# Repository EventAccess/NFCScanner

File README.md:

# NFCScanner
Maskinvare &amp; Firmware for in/ut-scanning

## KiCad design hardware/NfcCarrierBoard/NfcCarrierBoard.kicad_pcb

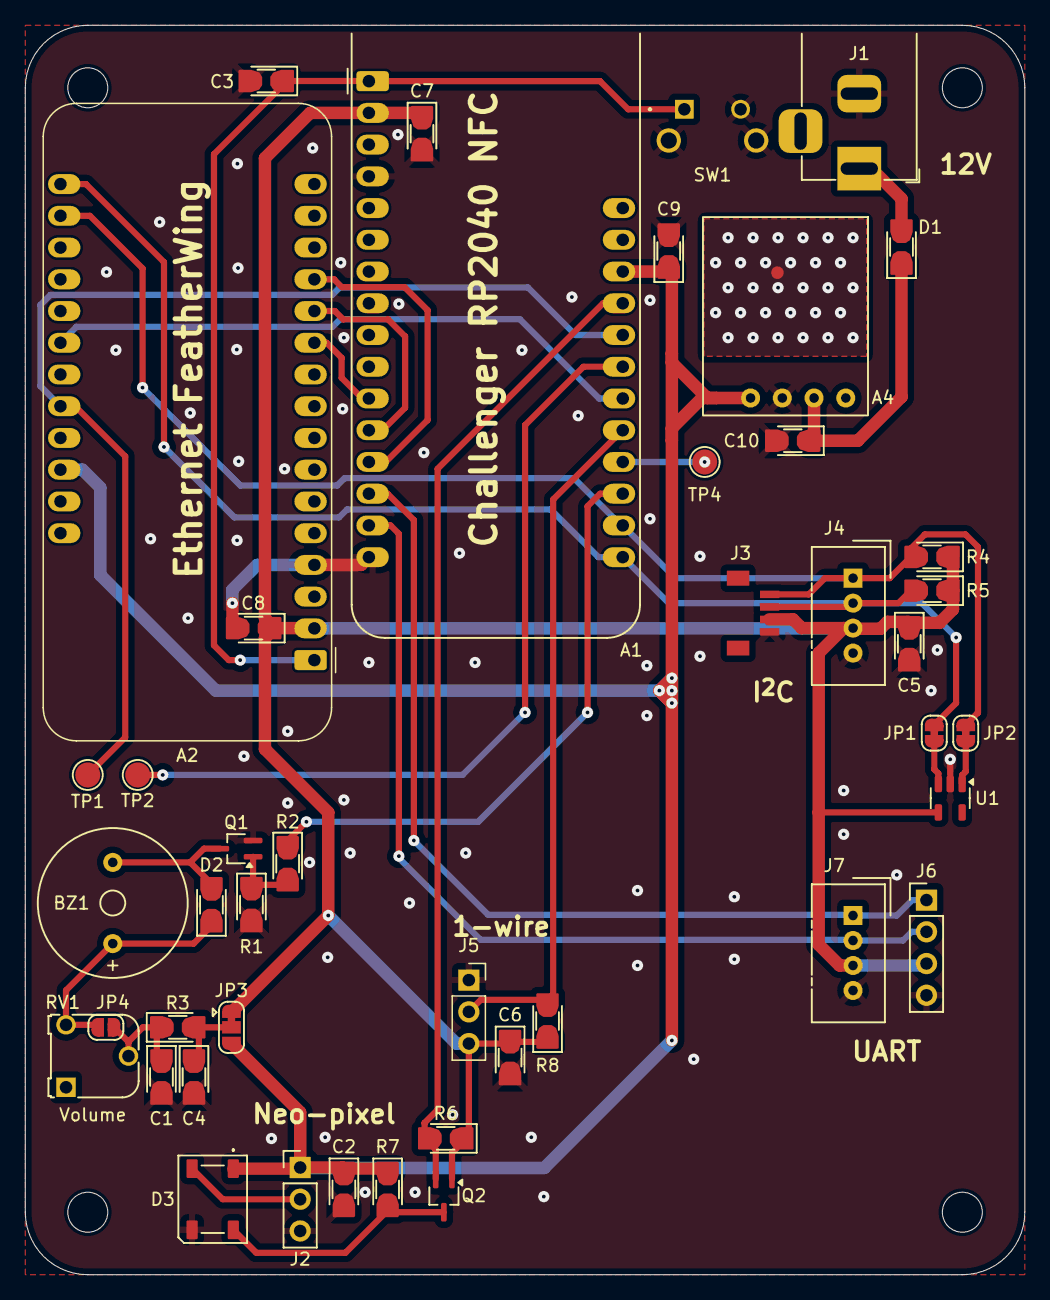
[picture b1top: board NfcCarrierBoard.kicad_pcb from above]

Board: 2 copper layers, 80.0 x 100.0 mm, 50 parts (1 on the bottom side), 29 nets.

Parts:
A1: iLabs Challenger RP2040 NFC; Adafruit_Feather
A2: Ethernet FeatherWing; Adafruit_Feather
A4: 5V 3A Buck Reg; SparkFun BabyBuck Regulator 5V
BZ1: Buzzer; Buzzer_PUIaudio_AT-1224-TWT_D12_H9_6.5mm
C1: 10µF; SMD_HANDSOLDER_UNIVERSAL_0603_0805_1206
C2, C3, C4, C5, C6, C7, C8, C9, C10: 0.1µF; SMD_HANDSOLDER_UNIVERSAL_0603_0805_1206
D1, D2: SL54A; SMD_HANDSOLDER_UNIVERSAL_0603_0805_1206
D3: WS2812B; LED_WS2812B_PLCC4_5.0x5.0mm_P3.2mm
H1, H2, H3, H4: MountingHole; MountingHole_3.2mm_M3
HS1: TestPoint; TestPoint_Pad_D1.0mm
J1: Barrel_Jack; BarrelJack_Horizontal
J2: Conn_01x03; PinHeader_1x03_P2.54mm_Vertical
J3: JST SH 4; JST-SH-4-top
J4: Grove; NS-Tech_Grove_1x04_P2mm_Vertical
J5: Conn_01x03; PinSocket_1x03_P2.54mm_Vertical
J6: UART; PinHeader_1x04_P2.54mm_Vertical
J7: Grove UART; NS-Tech_Grove_1x04_P2mm_Vertical
JP1, JP2: SolderJumper_2_Bridged; SolderJumper-2_P1.3mm_Bridged_RoundedPad1.0x1.5mm
JP3: SolderJumper_3_Bridged12; SolderJumper-3_P1.3mm_Bridged12_RoundedPad1.0x1.5mm
JP4: SolderJumper_2_Open; SolderJumper-2_P1.3mm_Open_RoundedPad1.0x1.5mm
Q1, Q2: NMOS; SOT-323_SC-70_Handsoldering
R1, R4, R5, R6, R7: 10kΩ; SMD_HANDSOLDER_UNIVERSAL_0603_0805_1206
R2: 330Ω; SMD_HANDSOLDER_UNIVERSAL_0603_0805_1206
R3: ~10Ω; SMD_HANDSOLDER_UNIVERSAL_0603_0805_1206
R8: 4.7kΩ; SMD_HANDSOLDER_UNIVERSAL_0603_0805_1206
RV1: R_Potentiometer_Trim; Potentiometer_Runtron_RM-065_Vertical
SW1: RESET; SW_TS11-674-105-BK-260-RA-D
SYM1: Logo_Open_Hardware_Small; OSHW-Logo_19x20mm_SilkScreen
TP1, TP2, TP4: TestPoint; TestPoint_Pad_D2.0mm
U1: 24AA02E48T; SOT-23-5

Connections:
1-Wire DQ: A1.21 (D9), J5.2, R8.2
+3.3V: A1.2 (3V3), A2.2 (3.3V), C5.1, C6.1, C7.1, C8.1, J3.2, J4.3, J5.3, J6.3, J7.3, JP3.1 (A), Q2.1 (G), R4.1, R5.1, R6.1, R8.1, U1.4 (V_{CC})
+5V: A1.26 (USB), A2.26 (PoE_5V), A4.4 (VOUT), C2.1, C9.1, D3.1 (VDD), J2.1, JP3.3 (B), R7.1
+12V: A4.2 (VIN), C10.1, D1.1 (K)
+12V Input: D1.2 (A), J1.1
BUZZER: A1.19 (D5), R2.1
Ethernet ~CS: A1.22 (D10), A2.22 (~CS)
Ethernet ~IRQ: A1.24 (D12), A2.24 (~IRQ), TP1.1
Ethernet ~RST: A1.23 (D11), TP2.1
GND: A1.4 (GND), A1.16 (GND), A2.4 (GND), A4.3 (GND), C1.2, C2.2, C3.2, C4.2, C5.2, C6.2, C7.2, C8.2, C9.2, C10.2, D3.3 (VSS), J1.2, J2.3, J3.1, J4.4, J5.1, J6.4, J7.4, Q1.2 (S), R1.2, SW1.2, SW1.SH (B), U1.2 (V_{SS})
NEO_DI: D3.4 (DIN), Q2.3 (D), R7.2
NEO_DI_LV: A1.25 (D13), Q2.2 (S), R6.2
NEO_DO: D3.2 (DOUT), J2.2
unnamed: A1.20 (D6), TP4.1
unnamed: BZ1.1 (+), D2.1 (K), JP4.1 (A), RV1.3
unnamed: BZ1.2 (-), D2.2 (A), Q1.3 (D)
unnamed: JP1.1 (A), U1.3 (SDA)
unnamed: JP2.1 (A), U1.1 (SCL)
unnamed: C4.1, JP3.2 (C), R3.2
unnamed: C1.1, JP4.2 (B), R3.1, RV1.2
unnamed: Q1.1 (G), R1.1, R2.2
RX: A1.14 (RX), J6.1, J7.1
SCK: A1.11 (SCK), A2.11 (SCK)
SCL: A1.18 (SCL), A2.18 (EEPROM_SCL), J3.4, J4.1, JP2.2 (B), R4.2
SDA: A1.17 (SDA), A2.17 (EEPROM_SDA), J3.3, J4.2, JP1.2 (B), R5.2
SDI: A1.13 (SDI), A2.13 (SDI)
SDO: A1.12 (SDO), A2.12 (SDO)
TX: A1.15 (TX), J6.2, J7.2
~RESET: A1.1 (~RESET), A2.1 (~reset_button), C3.1, SW1.1

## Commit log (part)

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2024-10-02 Add license
2024-10-02 Add devcontainer and IDE files
2024-10-02 Add todo2issue workflow
2024-10-02 Add todo
2024-10-03 Add editorconfig
2024-10-04 Improve devcontainer
2024-10-04 Add proof of concept sketches
    Modified from library example sketches to fit the ILABS Challenger RP2040 NFC
2024-10-06 Add CI build of examples
2024-10-06 Add ElectronicCats POC
2024-10-06 Change to custom fork of arduino-nfc
2024-10-14 Add script for installing tools
2024-10-14 Add renovate config
2024-10-15 Initial work on renovate updates for arduino dependencies
2024-10-19 Begin work on firmware
2024-10-19 Make HTTP connection more reliable
2024-10-19 Add EditorConfig extension to devcontainer
2024-10-24 Working POC app
2024-11-01 Remove some dead code
2024-11-19 Rename install -> install_tools
2024-11-19 Renovate: Add support for arduino boards manager
2024-11-19 Add tool to install arduino dependencies from manifest
2024-11-22 Initial work on carrier board
2024-12-27 README.md
2025-01-07 Configure DRC to hopefully match DirtyPCBs and JLC PCB
2025-01-07 Ignore rendered files
2025-01-07 Add BabyBuck regulator symbol
2025-01-07 Lots of schematic changes that should have been commited incrementally.
2025-01-07 Change 12V input symbol to jack with switch
2025-01-07 Add 1-Wire header
2025-01-09 Add decopuling caps
2025-01-10 Add PoE FeatherWing pinouts Add UART headers Fix some ERC errors
2025-01-11 Add SH-4-T (Quiic/STEMMA QT) connector 3D model Downloaded from https://www.digikey.no/en/models/1991988
    BM04B-SRSS-TBT
    JST Sales America Inc.
    CONN HEADER SMD 4POS 1MM
2025-01-11 Add SH-4-T connector footprint
2025-01-11 Add Buzzer footprint
2025-01-11 Change MOSFET symbols to match pinout of selected parts Add and select more footprints
2025-01-11 Add testpoint pads to unused pins
2025-01-11 Add jumper to select between 3.3V and 5V for audio
2025-01-11 Add autosave file to gitignore
2025-01-13 Add jumper to bypass audio pot
2025-01-13 Add custom footprint for the Ethernet FeatherWing
2025-01-13 Add mounting holes Add OSHW logo Change Ethernet footprint
2025-01-14 Add custom footprint for 0603 0805 1206 jellybean parts
2025-01-14 Add reset switch footprint and 3d model
2025-01-14 Update switch footprint to match KiCAD pin naming
2025-01-14 Link switch footprint to 3D model
2025-01-14 Begin work on PCB layout
2025-01-19 Populate more of the PCB Some DRC fixes
2025-01-19 Place last components
2025-01-19 Reduce some sharp angles on signal traces
2025-01-20 Add heatsink pad Add silkscreen
2025-01-21 Adjust silkscreen Expose heatsink pad
2025-01-21 Add script to render gerbers (and more)
2025-01-21 Fix rule errors
2025-01-21 Fix off-board silkscreen
2025-01-21 Render schematic pdf Export BOM
2025-01-21 Fix DirtyPCBs output
2025-01-21 Make rendered output appropriate for OSHPark and PCBWay
2025-01-21 Fix pdf rendering
2025-01-22 Populate part numbers for BOM
2025-01-26 DRC exclusions
2025-01-26 Populate resistors for BOM
2025-01-28 Populate capacitors for BOM
2025-01-30 Fix BOM output
2025-01-30 Remove reference to DirtyPCBs in zip filename
2025-02-05 Import updated BOM from schematic to PCB
2025-02-05 Add interactive BOM config
2025-02-06 Fix #42
2025-02-07 Read MAC address from EEPROM
    Fixes #11
2025-02-07 Add neopixel library
2025-02-07 Add buzzer beep
2025-02-07 Add Grove connector 3D model
2025-02-08 Create STEP 3D model of board
2025-02-08 Add Adafruit Ethernet FeatherWing 3D model
2025-02-08 Add buzzer 3D model
2025-02-08 Render 3D images of board using KiCAD nightly
2025-02-08 Change footprint for 1-wire header Not an electrical/physical board change, but this makes 3D renders show the proper connector
2025-02-08 Add header models to feather footprints
2025-02-09 Add BabyBuck board outline
2025-02-09 Start work on case design
2025-02-10 Case Base r1
2025-02-11 Case add top
2025-02-12 Case v1?
2025-02-12 Case Printed
2025-02-13 Add neopixel and buzzer output
2025-02-13 Include version number in firmware
2025-02-13 Move main code compilation steps to separate script
2025-02-13 Add print cost estimate
2025-02-13 Reducing this timeout increases the responsiveness
2025-02-14 Refractor away toHex
2025-02-15 Set http user agent
2025-02-27 Add support for https Split firmware into multiple files
2025-08-11 Update actions/checkout action to v5
2025-09-06 Update actions/setup-python action to v6
2025-11-21 Update dependency rp2040:rp2040 to v5
2025-11-22 Update actions/checkout action to v6
2025-11-22 Migrate config .github/renovate.json
2025-11-22 Add picture of finished prototype to readme
    Photo by @wiwivault (Instagram)
2025-11-22 Update dependency requests to v2.32.4 [SECURITY]
2026-02-17 Update dependency Electronic Cats PN7150 to v3
